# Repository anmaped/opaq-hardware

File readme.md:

# Hardware design files

* c1 - The main Opaq controller
* n1 - The node for dimming leds
* n2 - The power outlet node
* n3 - The wireless sensor node

All schematics and pcb designs are in eagle format.

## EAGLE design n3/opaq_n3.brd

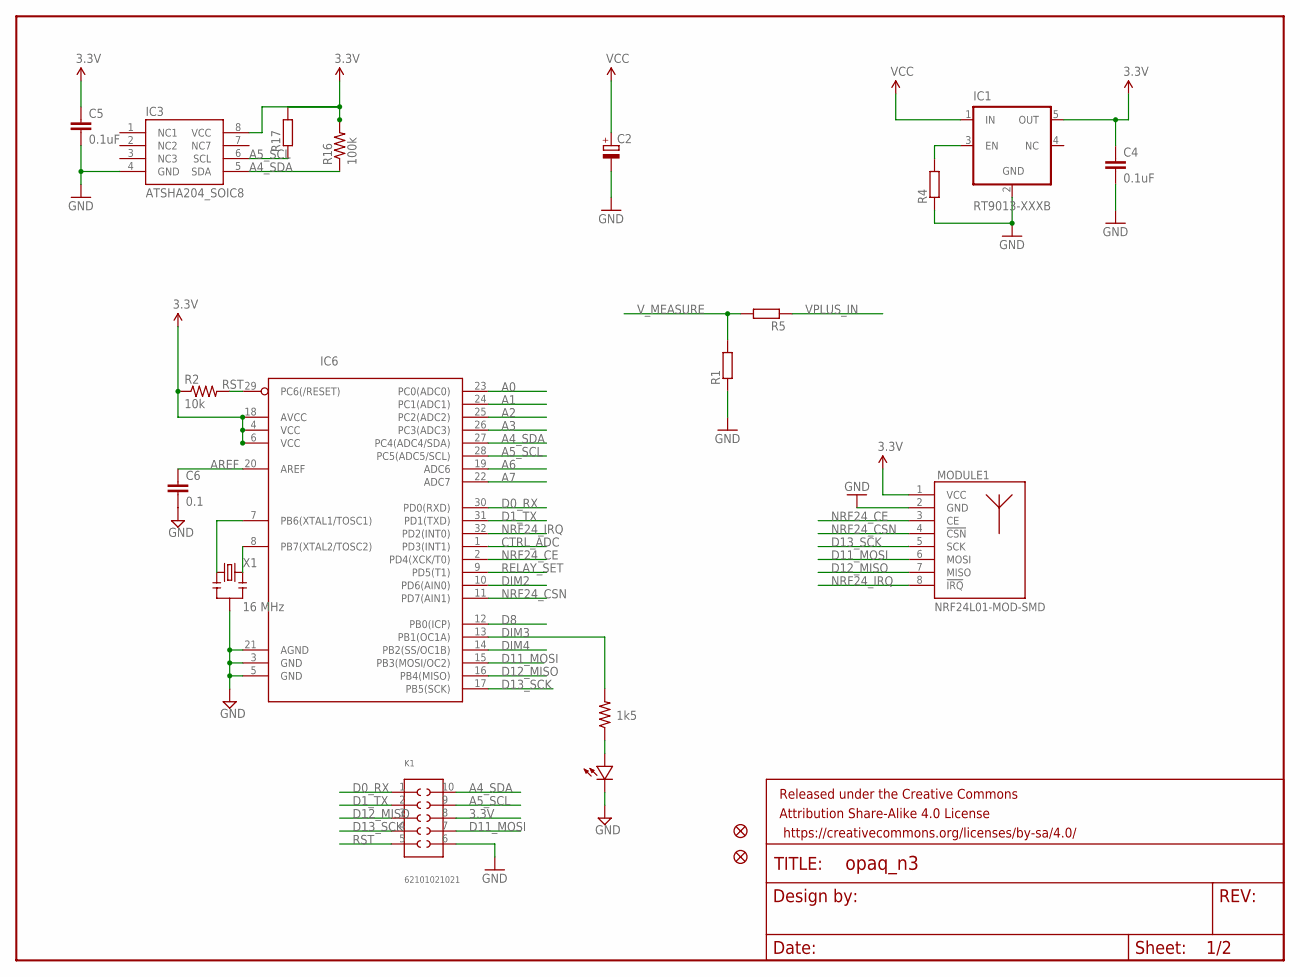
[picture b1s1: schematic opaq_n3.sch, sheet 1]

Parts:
C2: CPOL-EUC/6032-28R; C/6032-28R
C4, C5: 0.1uF; 0805
C6: 0.1; 0603-CAP
DIM: LED0603; 0603-LED
FRAME1: FRAME-LETTER; CREATIVE_COMMONS
IC1: RT9013-XXXB; SOT23-5
IC3: ATSHA204_SOIC8; SOIC8
IC6: ATMega-328; MLF32
JP1, JP2: FIDUCIAL1X2.5; FIDUCIAL-1X2.5
K1: 62101021021
MODULE1: NRF24L01-MOD-SMD; SMD8-MODULE
R1, R4, R5, R17: R-EU_R0805; 0805
R2: 10k; 0603-RES
R3: 1k5; 0603-RES
R16: 100k; 0805
X1: 16 MHz; RESONATOR-SMD

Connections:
3.3V: C4.1, C5.1, IC1.5 (OUT), IC3.8 (VCC), IC6.4 (VCC), IC6.6 (VCC), IC6.18 (AVCC), K1.8, MODULE1.1 (VCC), R2.1, R16.2, R17.2; also elsewhere on the board
A0: IC6.23 (PC0(ADC0))
A1: IC6.24 (PC1(ADC1))
A2: IC6.25 (PC2(ADC2))
A3: IC6.26 (PC3(ADC3))
A4_SDA: IC3.5 (SDA), IC6.27 (PC4(ADC4/SDA)), K1.10, R16.1; also elsewhere on the board
A5_SCL: IC3.6 (SCL), IC6.28 (PC5(ADC5/SCL)), K1.9, R17.1; also elsewhere on the board
A6: IC6.19 (ADC6)
A7: IC6.22 (ADC7)
AREF: C6.1, IC6.20 (AREF)
CTRL_ADC: IC6.1 (PD3(INT1)); also elsewhere on the board
D0_RX: IC6.30 (PD0(RXD)), K1.1
D1_TX: IC6.31 (PD1(TXD)), K1.2
D8: IC6.12 (PB0(ICP)); also elsewhere on the board
D11_MOSI: IC6.15 (PB3(MOSI/OC2)), K1.7, MODULE1.6 (MOSI); also elsewhere on the board
D12_MISO: IC6.16 (PB4(MISO)), K1.3, MODULE1.7 (MISO); also elsewhere on the board
D13_SCK: IC6.17 (PB5(SCK)), K1.4, MODULE1.5 (SCK); also elsewhere on the board
DIM2: IC6.10 (PD6(AIN0))
DIM3: IC6.13 (PB1(OC1A)), R3.2
DIM4: IC6.14 (PB2(SS/OC1B))
unnamed: IC6.7 (PB6(XTAL1/TOSC1)), X1.1
unnamed: DIM.PLUS, R3.1
unnamed: IC1.3 (EN), R4.2
unnamed: IC6.8 (PB7(XTAL2/TOSC2)), X1.3
NRF24_CE: IC6.2 (PD4(XCK/T0)), MODULE1.3 (CE)
NRF24_CSN: IC6.11 (PD7(AIN1)), MODULE1.4 (!CSN)
NRF24_IRQ: IC6.32 (PD2(INT0)), MODULE1.8 (!IRQ)
RELAY_SET: IC6.9 (PD5(T1))
RST: IC6.29 (PC6(/RESET)), K1.5, R2.2
VCC: C2.+, IC1.1 (IN)
VPLUS_IN: R5.1
V_MEASURE: R1.2, R5.2; also elsewhere on the board

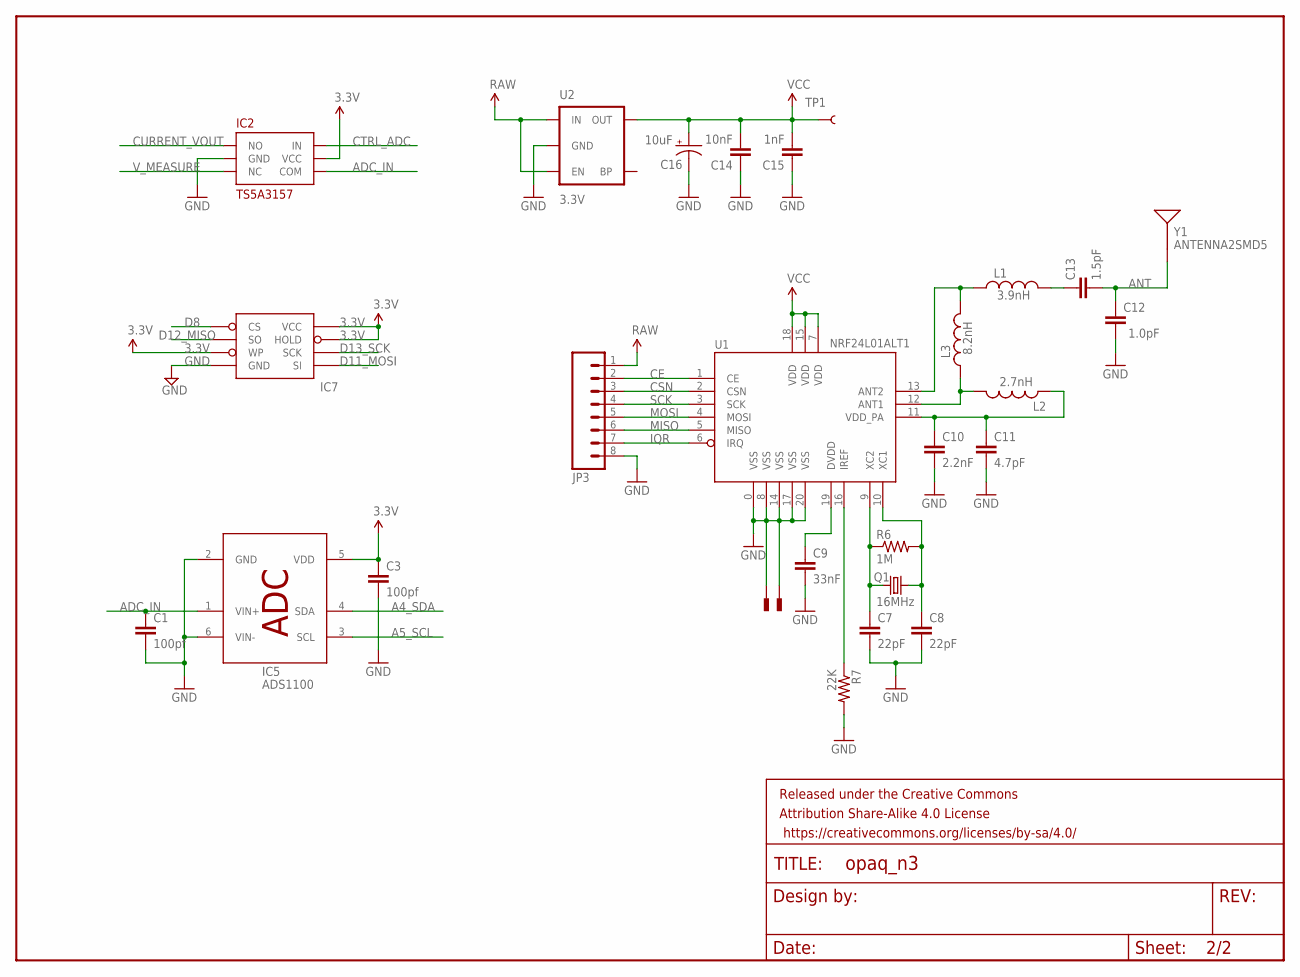
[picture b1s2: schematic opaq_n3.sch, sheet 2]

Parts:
C1, C3: 100pf; 0402-CAP
C7, C8: 22pF; 0402-CAP
C9: 33nF; 0402-CAP
C10: 2.2nF; 0402-CAP
C11: 4.7pF; 0402-CAP
C12: 1.0pF; 0402-CAP
C13: 1.5pF; 0402-CAP
C14: 10nF; 0402-CAP
C15: 1nF; 0402-CAP
C16: 10uF; EIA3216
FRAME2: FRAME-LETTERNO_PACKAGE; DUMMY
IC2: TS5A3157; SOT23-6
IC5: ADS1100; SOT23-6
IC7: AT25F512BWIDE_5.3MM; SO08WIDE
JP3: M081X08; 1X08
L1: 3.9nH; C0402
L2: 2.7nH; C0402
L3: 8.2nH; C0402
Q1: 16MHz; CRYSTAL-SMD-5X3
R6: 1M; 0402-RES
R7: 22K; 0402-RES
TP1: TEST-POINT3X5; PAD.03X.05
U1: NRF24L01ALT1; QFN20_ALT1
U2: 3.3V; SOT23-5
U$1, U$4: PAD; PAD-0.008
Y1: ANTENNA2SMD5; ANTENNA-CHIP5

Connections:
3.3V: C3.1, IC2.5 (VCC), IC5.5 (VDD), IC7.3 (WP), IC7.7 (HOLD), IC7.8 (VCC); also elsewhere on the board
A4_SDA: IC5.4 (SDA); also elsewhere on the board
A5_SCL: IC5.3 (SCL); also elsewhere on the board
ADC_IN: C1.1, IC2.4 (COM), IC5.1 (VIN+)
ANT: C12.2, C13.2, Y1.FEED
CE: JP3.2, U1.1 (CE)
CSN: JP3.3, U1.2 (CSN)
CTRL_ADC: IC2.6 (IN); also elsewhere on the board
CURRENT_VOUT: IC2.1 (NO)
D8: IC7.1 (CS); also elsewhere on the board
D11_MOSI: IC7.5 (SI); also elsewhere on the board
D12_MISO: IC7.2 (SO); also elsewhere on the board
D13_SCK: IC7.6 (SCK); also elsewhere on the board
IQR: JP3.7, U1.6 (IRQ)
MISO: JP3.6, U1.5 (MISO)
MOSI: JP3.5, U1.4 (MOSI)
unnamed: C7.1, Q1.1, R6.1, U1.9 (XC2)
unnamed: C8.1, Q1.3 (2), R6.2, U1.10 (XC1)
unnamed: R7.1, U1.16 (IREF)
unnamed: L1.1, L3.2, U1.13 (ANT2)
unnamed: C10.1, C11.1, L2.1, U1.11 (VDD_PA)
unnamed: C9.1, U1.19 (DVDD)
unnamed: L2.2, L3.1, U1.12 (ANT1)
unnamed: C13.1, L1.2
RAW: JP3.1, U2.1 (IN), U2.3 (EN)
SCK: JP3.4, U1.3 (SCK)
VCC1: C14.2, C15.2, C16.A (+), TP1.P$1, U1.7 (VDD), U1.15 (VDD), U1.18 (VDD), U2.5 (OUT)
V_MEASURE: IC2.3 (NC); also elsewhere on the board

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
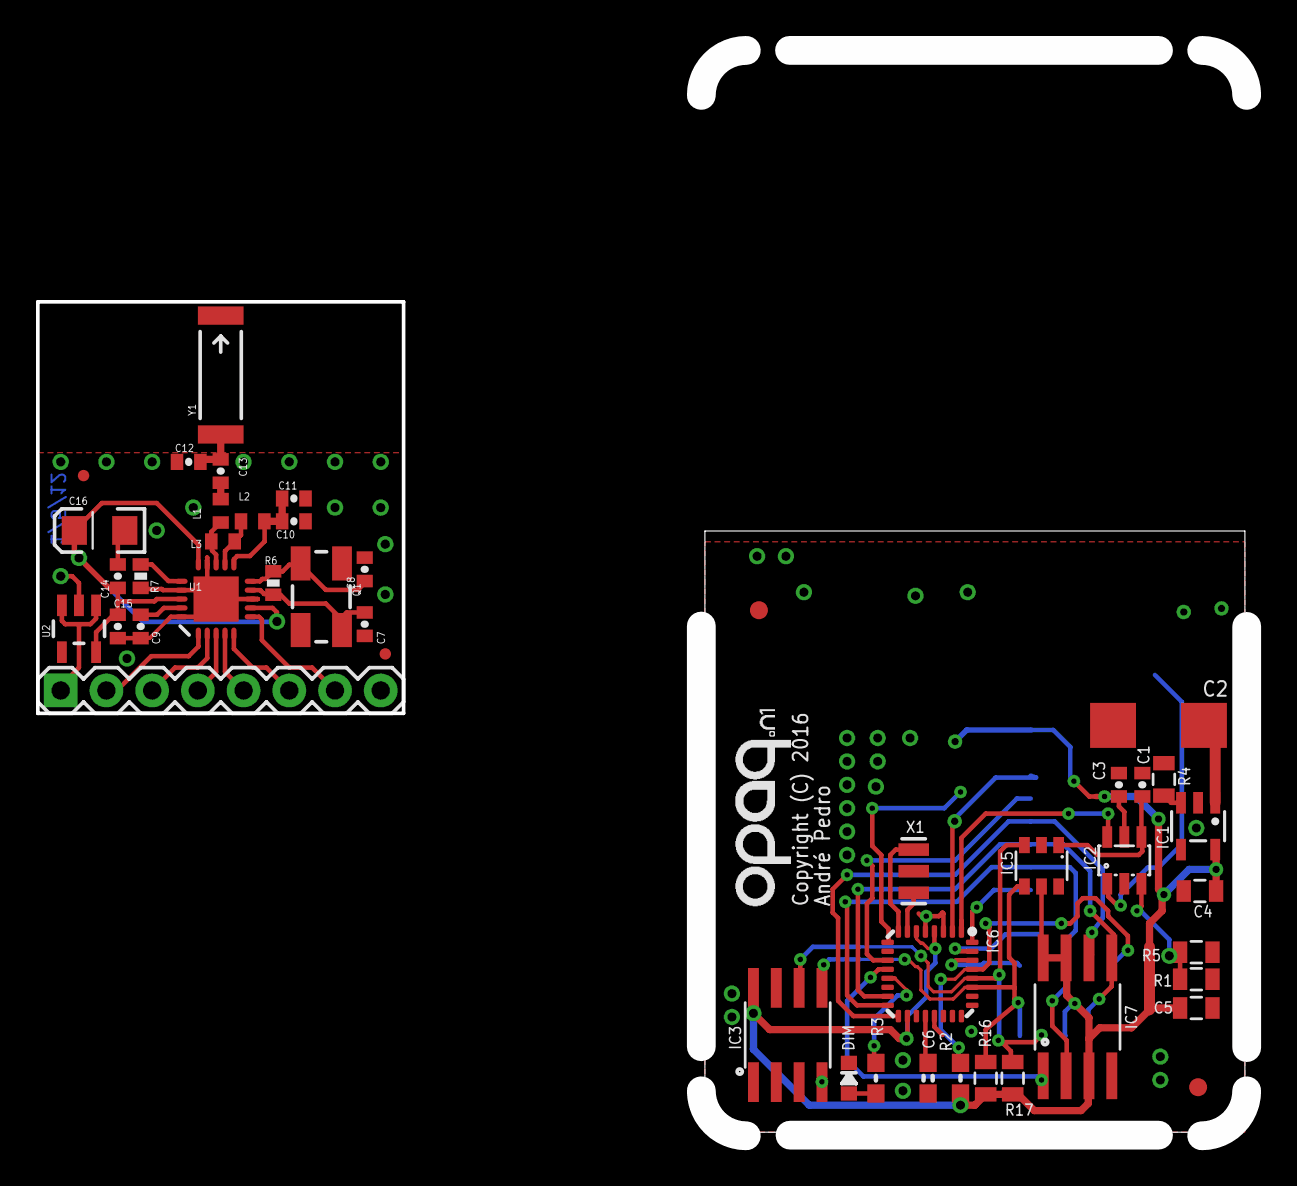
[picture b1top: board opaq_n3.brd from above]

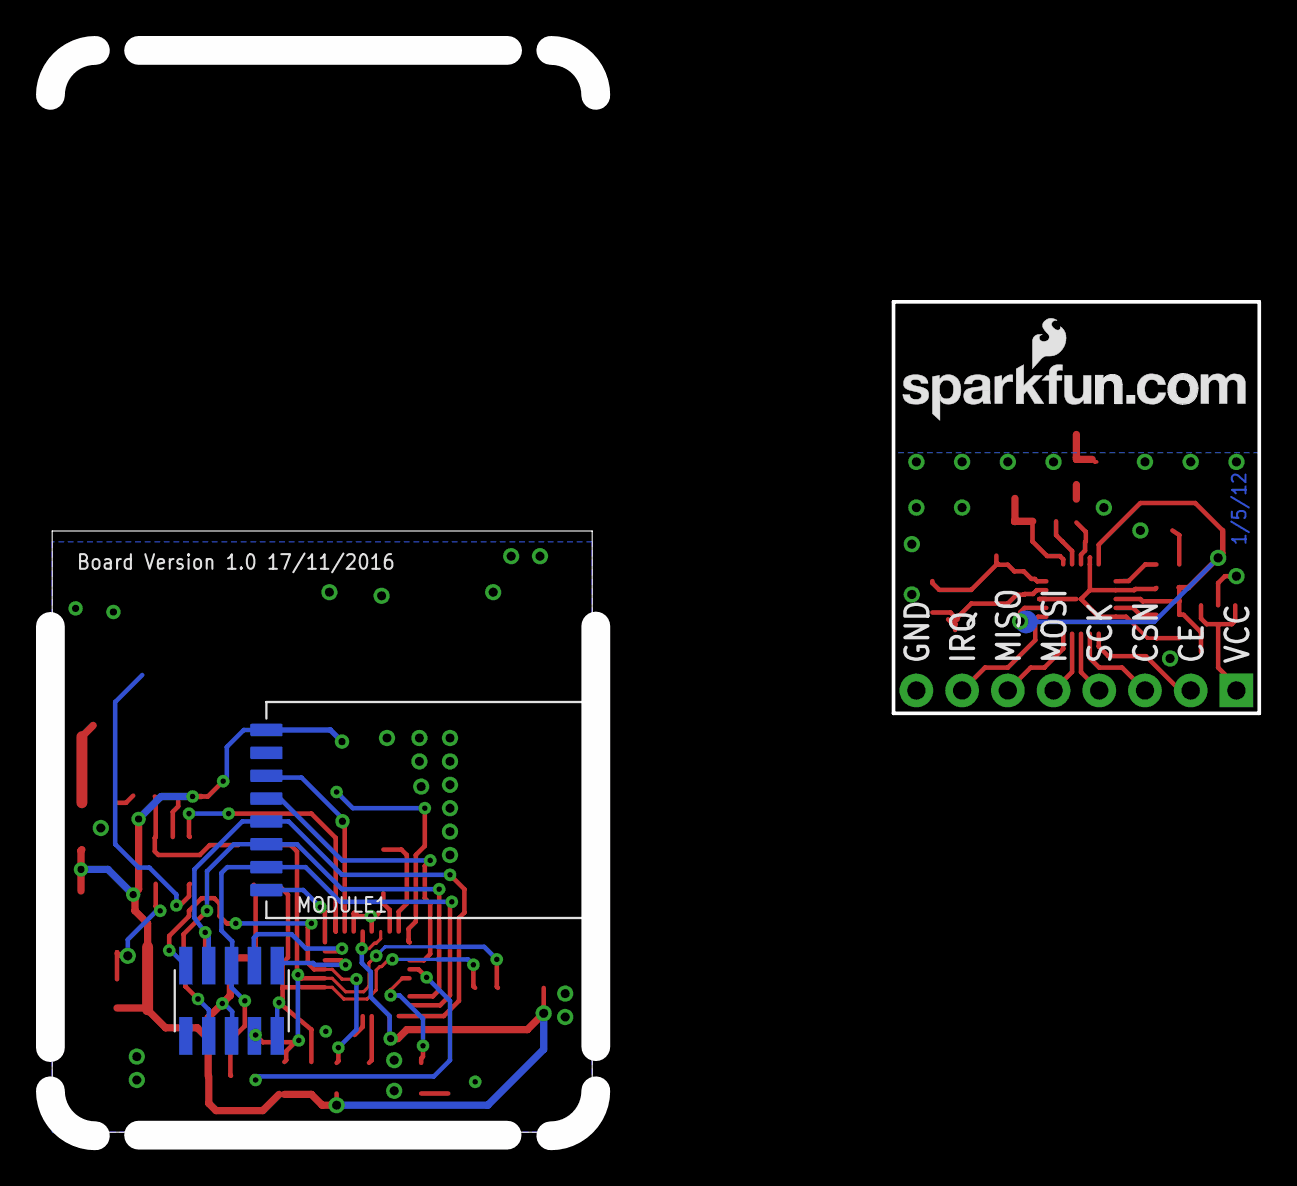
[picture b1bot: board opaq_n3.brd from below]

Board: 2 copper layers, 67.2 x 60.3 mm, 53 parts (4 on the bottom side), 42 nets.

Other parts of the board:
JP4, JP5: FIDUCIALUFIDUCIAL; MICRO-FIDUCIAL
U$5: LOGO-SFENEW; SFE-NEW-WEBLOGO

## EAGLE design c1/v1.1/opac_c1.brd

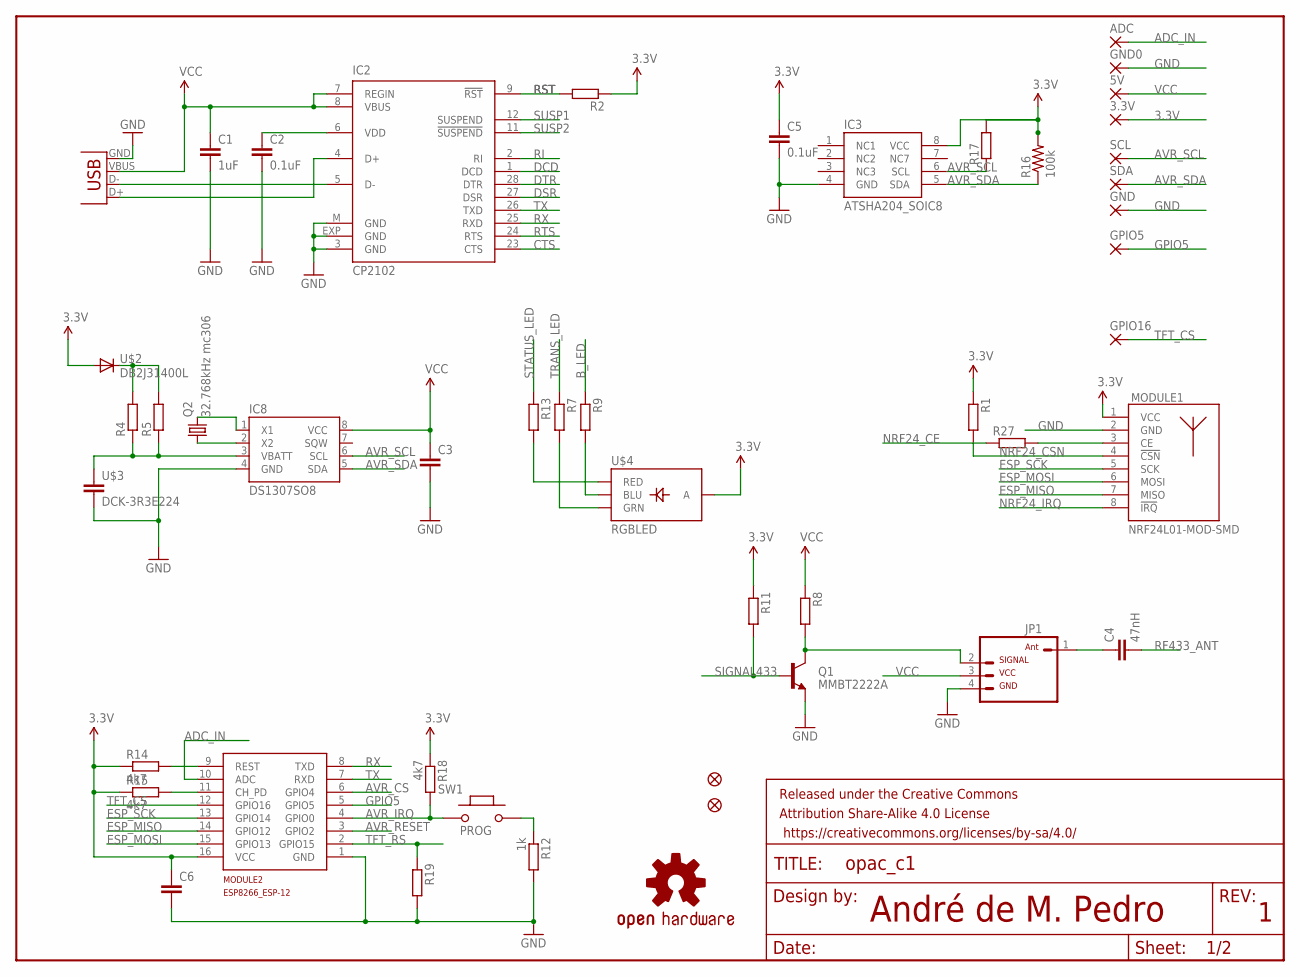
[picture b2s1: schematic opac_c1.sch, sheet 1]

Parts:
3.3V, 5V: SMD2; SMD1,27-2,54
ADC: SMD2; SMD1,27-2,54
C1: 1uF; 0603
C2: 0.1uF; 0603
C3, C6: C-EUC0805K; C0805K
C4: 47nH; C0603K
C5: 0.1uF; 0805
FRAME1: FRAME-LETTER; CREATIVE_COMMONS
GND, GND0: SMD2; SMD1,27-2,54
GPIO5, GPIO16: SMD2; SMD1,27-2,54
IC2: CP2102; MLP28
IC3: ATSHA204_SOIC8; SOIC8
IC8: DS1307SO8; SO08
JP1: RF433SMD; 1X04-SMD
JP2, JP3: FIDUCIAL1X2.5; FIDUCIAL-1X2.5
LOGO1: OSHW-LOGOL; OSHW-LOGO-L
MODULE1: NRF24L01-MOD-SMD; SMD8-MODULE
MODULE2: ESP8266_ESP-12; ESP8266-ESP12
Q1: MMBT2222A; SOT23-3
Q2: 32.768kHz mc306; MC-306
R1, R4, R5, R8, R11, R17, R19, R27: R-EU_R0805; 0805
R2, R7, R9, R13: R-EU_R0603; R0603
R12: 1k; 0805
R14, R15, R18: 4k7; 0805
R16: 100k; 0805
SCL: SMD2; SMD1,27-2,54
SDA: SMD2; SMD1,27-2,54
SW1: PROG; 157SW; PARTNO RS 682-1421
U$2: DB2J31400L; SMINI2-F5-B
U$3: DCK-3R3E224
U$4: RGBLED; RGBLED0603
USB1: USB-MICROB

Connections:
3.3V: 3.3V.1, C5.1, C6.1, IC3.8 (VCC), MODULE1.1 (VCC), MODULE2.16 (VCC), R1.1, R2.1, R11.1, R14.1, R15.1, R16.2, R17.2, R18.1, U$2.P$2 (A), U$4.P$3 (A); also elsewhere on the board
ADC_IN: ADC.1, MODULE2.10 (ADC)
AVR_CS: MODULE2.6 (GPIO4); also elsewhere on the board
AVR_IRQ: MODULE2.4 (GPIO0), R18.2, SW1.1; also elsewhere on the board
AVR_RESET: MODULE2.3 (GPIO2); also elsewhere on the board
AVR_SCL: IC3.6 (SCL), IC8.6 (SCL), R17.1, SCL.1; also elsewhere on the board
AVR_SDA: IC3.5 (SDA), IC8.5 (SDA), R16.1, SDA.1; also elsewhere on the board
B_LED: R9.1; also elsewhere on the board
CTS: IC2.23 (CTS)
DCD: IC2.1 (DCD)
DSR: IC2.27 (DSR)
DTR: IC2.28 (DTR)
ESP_MISO: MODULE1.7 (MISO), MODULE2.14 (GPIO12); also elsewhere on the board
ESP_MOSI: MODULE1.6 (MOSI), MODULE2.15 (GPIO13); also elsewhere on the board
ESP_SCK: MODULE1.5 (SCK), MODULE2.13 (GPIO14); also elsewhere on the board
GND: C1.2, C2.2, C3.2, C5.2, C6.2, GND.1, GND0.1, IC2.3 (GND), IC2.EXP (GND), IC2.M (GND), IC3.4 (GND), IC8.4 (GND), JP1.4 (2), MODULE1.2 (GND), MODULE2.1 (GND), Q1.2 (E), R12.2, R19.2, U$3.P$1 (2), USB1.GND; also elsewhere on the board
GPIO5: GPIO5.1, MODULE2.5 (GPIO5)
unnamed: IC8.3 (VBATT), R4.1, R5.1, U$3.P$2 (1)
unnamed: IC8.2 (X2), Q2.1
unnamed: R4.2, R5.2, U$2.P$1 (C)
unnamed: C2.1, IC2.6 (VDD)
unnamed: IC8.1 (X1), Q2.4 (2)
unnamed: R13.2, U$4.P$1 (RED)
unnamed: R12.1, SW1.2
unnamed: IC2.5 (D-), USB1.D-
unnamed: R7.2, U$4.P$2 (GRN)
unnamed: IC2.4 (D+), USB1.D+
unnamed: JP1.2 (3), Q1.3 (C), R8.2
unnamed: R9.2, U$4.P$4 (BLU)
unnamed: MODULE1.3 (CE), R27.2
unnamed: C4.1, JP1.1 (4)
unnamed: MODULE2.9 (REST), R14.2
unnamed: MODULE2.11 (CH_PD), R15.2
NRF24_CE: R27.1; also elsewhere on the board
NRF24_CSN: MODULE1.4 (!CSN), R1.2; also elsewhere on the board
NRF24_IRQ: MODULE1.8 (!IRQ); also elsewhere on the board
RF433_ANT: C4.2
RI: IC2.2 (RI)
RST: IC2.9 (!RST), R2.2
RTS: IC2.24 (RTS)
RX: IC2.25 (RXD), MODULE2.8 (TXD)
SIGNAL433: Q1.1 (B), R11.2; also elsewhere on the board
STATUS_LED: R13.1; also elsewhere on the board
SUSP1: IC2.12 (SUSPEND)
SUSP2: IC2.11 (!SUSPEND)
TFT_CS: GPIO16.1, MODULE2.12 (GPIO16); also elsewhere on the board
TFT_RS: MODULE2.2 (GPIO15), R19.1; also elsewhere on the board
TRANS_LED: R7.1; also elsewhere on the board
TX: IC2.26 (TXD), MODULE2.7 (RXD)
VCC: 5V.1, C1.1, C3.1, IC2.7 (REGIN), IC2.8 (VBUS), IC8.8 (VCC), JP1.3 (1), R8.1, USB1.VBUS; also elsewhere on the board

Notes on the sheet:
André de M. Pedro

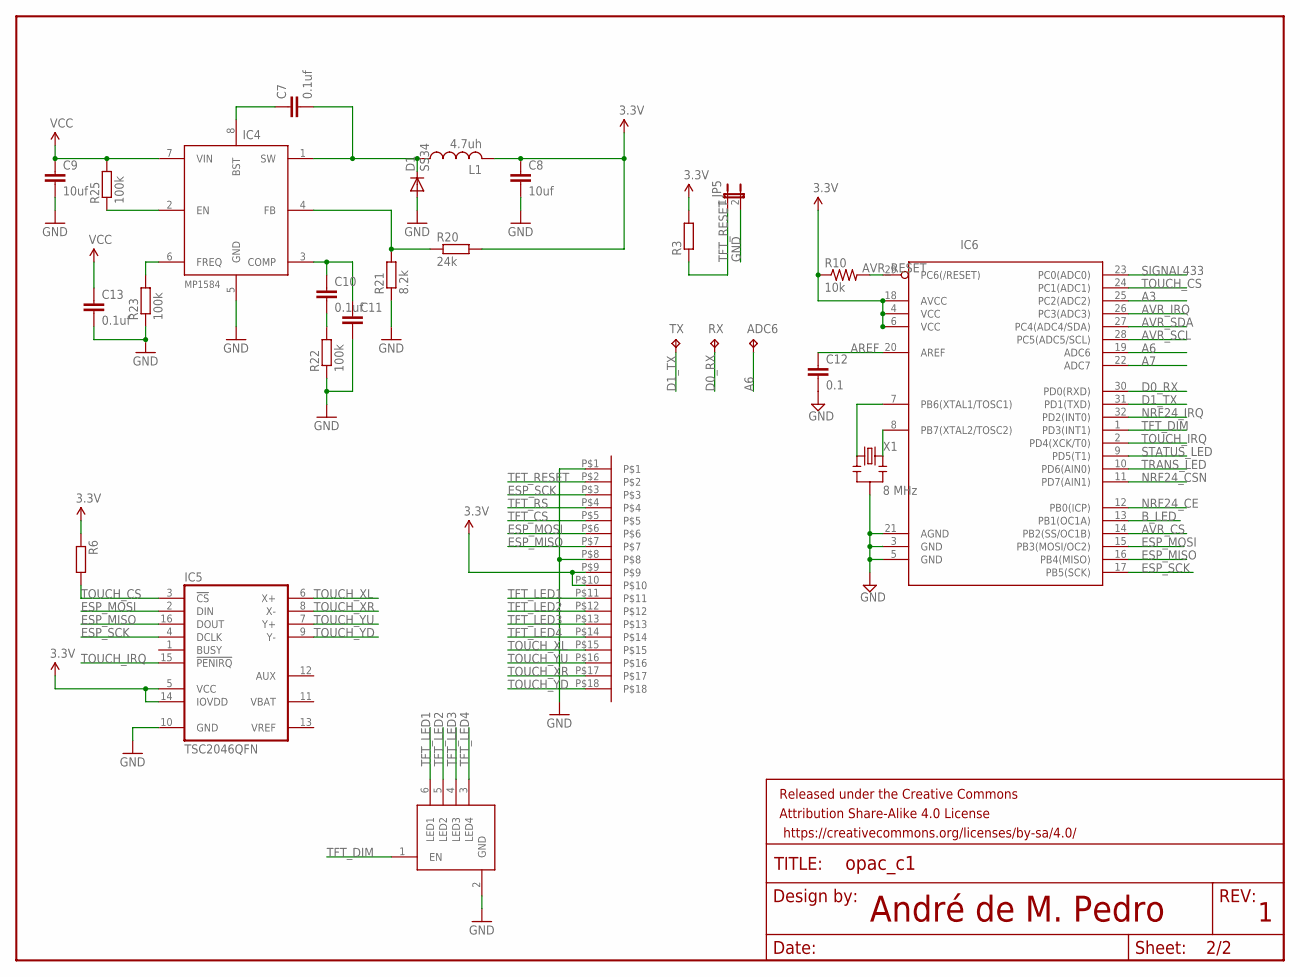
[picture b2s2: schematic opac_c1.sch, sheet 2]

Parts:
ADC6: TPTP09R; TP09R
C7, C10, C13: 0.1uf; C0603
C8, C9: 10uf; C3216
C11: C-EUC0603; C0603
C12: 0.1; 0805
D1: SS34; SMA-DIODE
FRAME2: FRAME-LETTER; CREATIVE_COMMONS
IC4: MP1584; SO08-EPAD
IC5: TSC2046QFN; QFN16-4X4
IC6: ATMega-328; MLF32
IC7: RT9300; SOT23-6
JP5: JUMPER-2SMD-NO; SJ_2S-NO
L1: 4.7uh; 2525
R3: R-EU_R0402; R0402
R6: R-EU_R0805; 0805
R10: 10k; 0603-RES
R20: 24k; R0603
R21: 8.2k; R0603
R22, R23, R25: 100k; R0603
RX: TPTP10SQ; TP10SQ
TX: TPTP10SQ; TP10SQ
U$1: CONNECTOR8P0.8; CONNECTOR18P0.8
X1: 8 MHz; RESONATOR-SMD

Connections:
3.3V: C8.1, IC5.5 (VCC), IC5.14 (IOVDD), IC6.4 (VCC), IC6.6 (VCC), IC6.18 (AVCC), L1.P$1, R3.2, R6.1, R10.1, R20.2, U$1.P$9, U$1.P$10; also elsewhere on the board
A3: IC6.25 (PC2(ADC2))
A6: ADC6.TP, IC6.19 (ADC6)
A7: IC6.22 (ADC7)
AREF: C12.1, IC6.20 (AREF)
AVR_CS: IC6.14 (PB2(SS/OC1B)); also elsewhere on the board
AVR_IRQ: IC6.26 (PC3(ADC3)); also elsewhere on the board
AVR_RESET: IC6.29 (PC6(/RESET)), R10.2; also elsewhere on the board
AVR_SCL: IC6.28 (PC5(ADC5/SCL)); also elsewhere on the board
AVR_SDA: IC6.27 (PC4(ADC4/SDA)); also elsewhere on the board
B_LED: IC6.13 (PB1(OC1A)); also elsewhere on the board
D0_RX: IC6.30 (PD0(RXD)), RX.TP
D1_TX: IC6.31 (PD1(TXD)), TX.TP
ESP_MISO: IC5.16 (DOUT), IC6.16 (PB4(MISO)), U$1.P$7; also elsewhere on the board
ESP_MOSI: IC5.2 (DIN), IC6.15 (PB3(MOSI/OC2)), U$1.P$6; also elsewhere on the board
ESP_SCK: IC5.4 (DCLK), IC6.17 (PB5(SCK)), U$1.P$3; also elsewhere on the board
GND: C8.2, C9.2, C11.2, C12.2, C13.2, D1.A, IC4.5 (GND), IC5.10 (GND), IC6.3 (GND), IC6.5 (GND), IC6.21 (AGND), IC7.2 (GND), JP5.2, R21.1, R22.1, R23.1, U$1.P$1, U$1.P$8, X1.2; also elsewhere on the board
unnamed: IC6.7 (PB6(XTAL1/TOSC1)), X1.1
unnamed: IC6.8 (PB7(XTAL2/TOSC2)), X1.3
unnamed: C7.2, D1.C, IC4.1 (SW), L1.P$2
unnamed: C7.1, IC4.8 (BST)
unnamed: IC4.4 (FB), R20.1, R21.2
unnamed: IC4.2 (EN), R25.1
unnamed: IC4.6 (FREQ), R23.2
unnamed: C10.1, C11.1, IC4.3 (COMP)
unnamed: C10.2, R22.2
NRF24_CE: IC6.12 (PB0(ICP)); also elsewhere on the board
NRF24_CSN: IC6.11 (PD7(AIN1)); also elsewhere on the board
NRF24_IRQ: IC6.32 (PD2(INT0)); also elsewhere on the board
SIGNAL433: IC6.23 (PC0(ADC0)); also elsewhere on the board
STATUS_LED: IC6.9 (PD5(T1)); also elsewhere on the board
TFT_CS: U$1.P$5; also elsewhere on the board
TFT_DIM: IC6.1 (PD3(INT1)), IC7.1 (EN)
TFT_LED1: IC7.6 (LED1), U$1.P$11
TFT_LED2: IC7.5 (LED2), U$1.P$12
TFT_LED3: IC7.4 (LED3), U$1.P$13
TFT_LED4: IC7.3 (LED4), U$1.P$14
TFT_RESET: JP5.1, R3.1, U$1.P$2
TFT_RS: U$1.P$4; also elsewhere on the board
TOUCH_CS: IC5.3 (!CS), IC6.24 (PC1(ADC1)), R6.2
TOUCH_IRQ: IC5.15 (!PENIRQ), IC6.2 (PD4(XCK/T0))
TOUCH_XL: IC5.6 (X+), U$1.P$15
TOUCH_XR: IC5.8 (X-), U$1.P$17
TOUCH_YD: IC5.9 (Y-), U$1.P$18
TOUCH_YU: IC5.7 (Y+), U$1.P$16
TRANS_LED: IC6.10 (PD6(AIN0)); also elsewhere on the board
VCC: C9.1, C13.1, IC4.7 (VIN), R25.2; also elsewhere on the board

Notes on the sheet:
André de M. Pedro

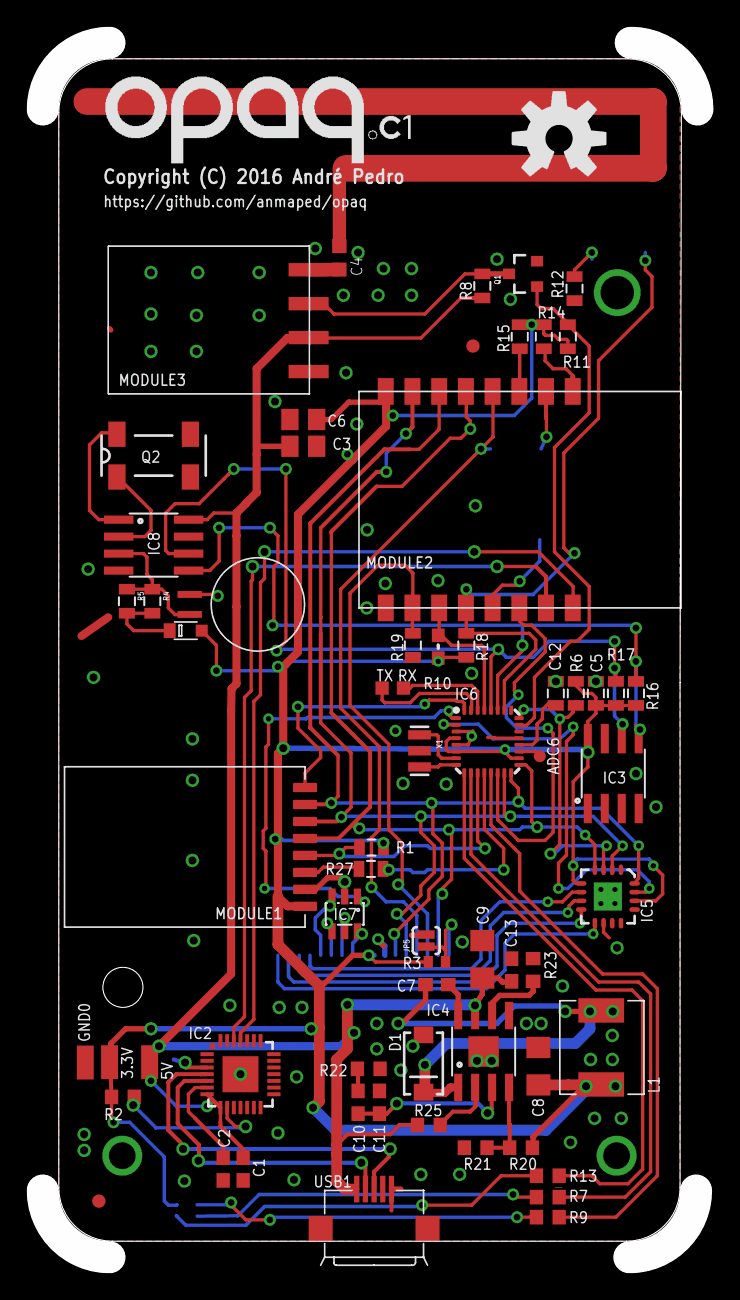
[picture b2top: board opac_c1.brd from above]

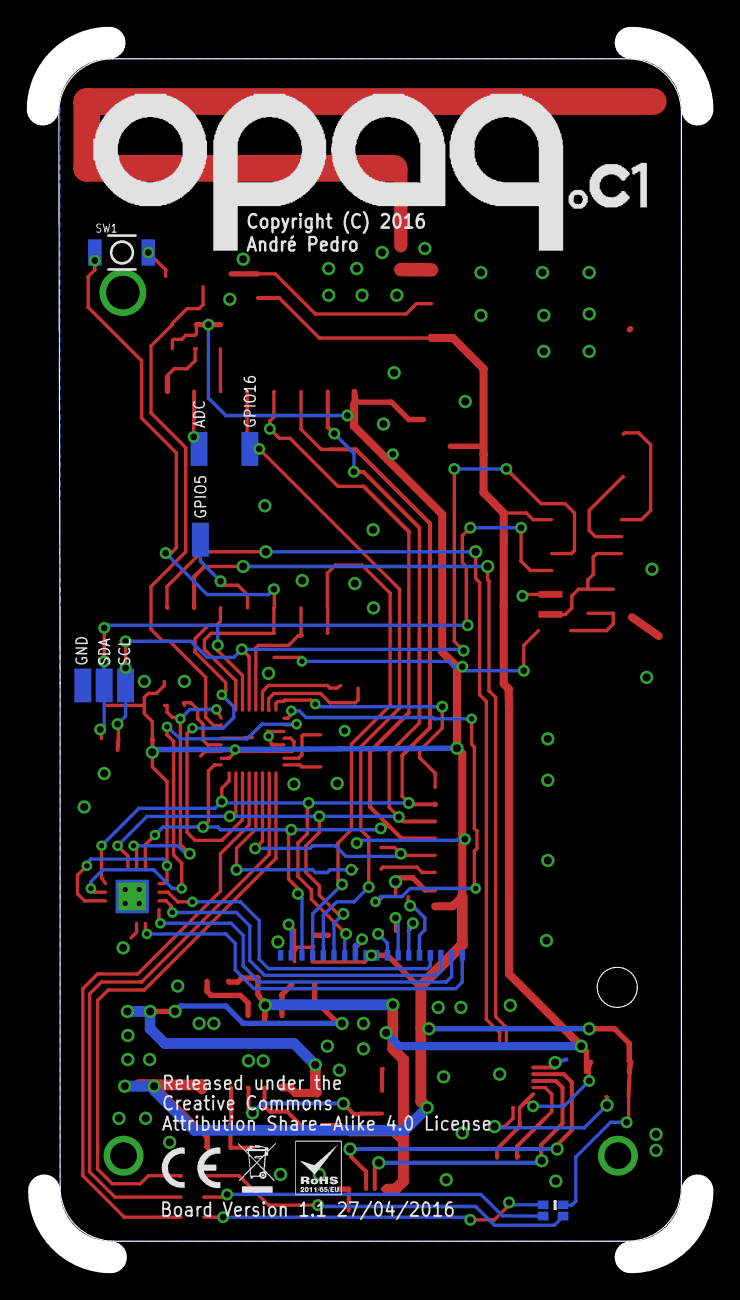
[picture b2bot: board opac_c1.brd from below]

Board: 2 copper layers, 49.0 x 90.9 mm, 77 parts (9 on the bottom side), 66 nets.

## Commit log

2015-11-04 Opaq C1 board v1.0 has released. Source-files are available over the CC-SA license.
2015-11-04 Revision 1 of opac.c1 board.
2015-11-05 Opaq.c1 revision 2.
2015-11-18 Opac n1 hardware released.
2015-11-19 Opaq n1 board revision 1.
2015-11-22 Opaq C1 hardware revision 3.
2015-11-24 Opaq n1 hardware revision 2.
2016-05-10 Opaq c1 version 1.1 has been released.
2016-05-10 Opaq n1 version 2.1 has been released.
2016-07-02 Opaq c1 supports iaqua graphical interface.
    The touch screen and the 320x240 tft is now supported.
    Added features:
    - file storage manager using JSON for opaq settings.
    - touch screen calibration.
    - coprocessor program to interact with real-time clock, cypher chip (SHA204), and expansion of the GPIO.
    - ISP programmer for AVR coprocessor.
2016-07-02 Several issues of the Opaq c1 hardware have been fixed.
2016-07-04 Opaq c1 hardware has been updated.
    - pull-up resistor have been added to RF433 signal.
2016-08-13 Added the new fixes for opaq c1 hardware.
2016-08-23 Updated version of the opaq c1 hardware.
2016-10-31 Renamed folders from 'opaq_c1' to 'c1' and 'opaq_n1' to 'n1'.
2016-10-31 Updated opaq n2 schematic and board files.
2016-11-15 Small changes of the opaq n1 board.
2016-11-17 Updated opaq n2 hardware. Isolated power supply has been added.
2016-11-26 Candidate version of opaq n2 for pcb production.
2016-12-12 Opaq n2 hardware version r1.
2018-08-22 Uncompleted version of opaq n3.
2018-08-23 Create readme.md
    The inclusion of a readme file.

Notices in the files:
c1/v1.1/opac_c1.brd:
Copyright (C) 2016 André Pedro
Released under the
Creative Commons
Attribution Share-Alike 4.0 License
parts and their libraries:
SparkFun-DigitalIC: Licensing: CC v3.0 Share-Alike You are welcome to use this library for commercial purposes.
SparkFun-Aesthetics: Released under the Creative Commons Attribution Share-Alike 4.0 License
SparkFun-Aesthetics: https://creativecommons.org/licenses/by-sa/4.0
